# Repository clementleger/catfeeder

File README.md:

catfeeder
=========

Arduino scripts for cat feeder

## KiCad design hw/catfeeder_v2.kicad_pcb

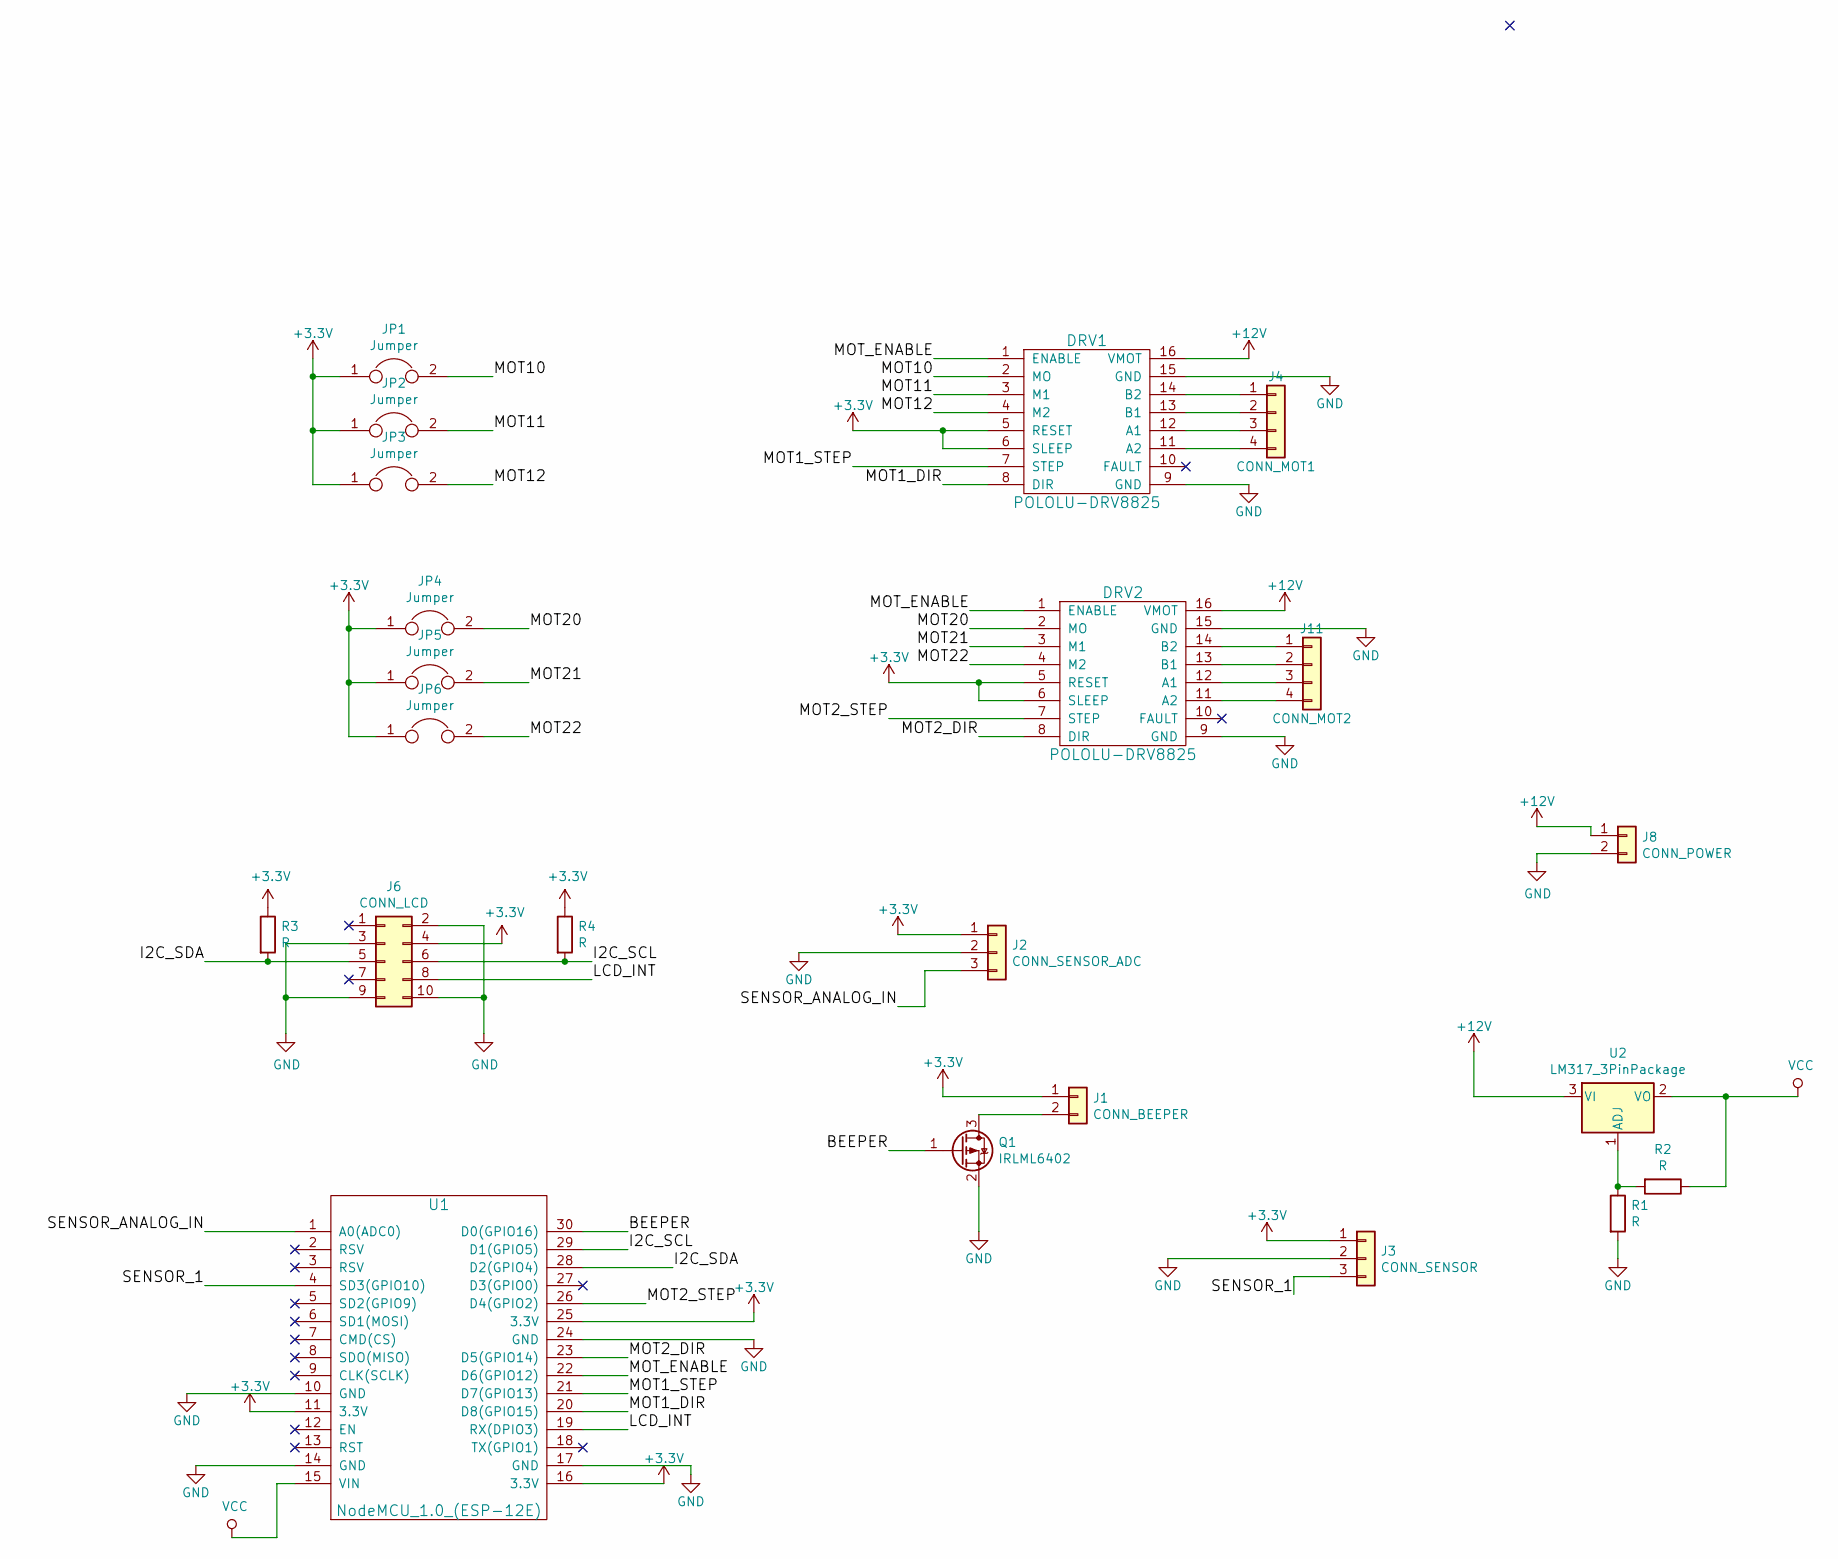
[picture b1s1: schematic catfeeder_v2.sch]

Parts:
DRV1, DRV2: POLOLU-DRV8825
J1: CONN_BEEPER; JST_XH_B02B-XH-A_1x02_P2.50mm_Vertical
J2: CONN_SENSOR_ADC; JST_XH_B03B-XH-A_1x03_P2.50mm_Vertical
J3: CONN_SENSOR; JST_XH_B03B-XH-A_1x03_P2.50mm_Vertical
J4: CONN_MOT1; JST_XH_B04B-XH-A_1x04_P2.50mm_Vertical
J6: CONN_LCD; IDC-Header_2x05_P2.54mm_Vertical
J8: CONN_POWER; TerminalBlock_bornier-2_P5.08mm
J11: CONN_MOT2; JST_XH_B04B-XH-A_1x04_P2.50mm_Vertical
JP1, JP2, JP3, JP4, JP5, JP6: Jumper; R_0805_2012Metric_Pad1.15x1.40mm_HandSolder
Q1: IRLML6402; SOT-23
R1, R2: R; R_0805_2012Metric_Pad1.15x1.40mm_HandSolder
R3, R4: R; R_Axial_DIN0207_L6.3mm_D2.5mm_P10.16mm_Horizontal
U1: NodeMCU_1.0_(ESP-12E); ESP12F-Devkit-V3
U2: LM317_3PinPackage; TO-220-3_Vertical

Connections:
+3V3: DRV1.5 (RESET), DRV1.6 (SLEEP), DRV2.5 (RESET), DRV2.6 (SLEEP), J1.1, J2.1, J3.1, J6.4, JP1.1, JP2.1, JP3.1, JP4.1, JP5.1, JP6.1, R3.1, R4.1, U1.11 (3.3V), U1.16 (3.3V), U1.25 (3.3V)
+12V: DRV1.16 (VMOT), DRV2.16 (VMOT), J8.1, U2.3 (VI)
/BEEPER: Q1.1 (G), U1.30 (D0(GPIO16))
/I2C_SCL: J6.6, R4.2, U1.29 (D1(GPIO5))
/I2C_SDA: J6.5, R3.2, U1.28 (D2(GPIO4))
/LCD_INT: J6.8, U1.19 (RX(DPIO3))
/MOT1_DIR: DRV1.8 (DIR), U1.20 (D8(GPIO15))
/MOT1_STEP: DRV1.7 (STEP), U1.21 (D7(GPIO13))
/MOT2_DIR: DRV2.8 (DIR), U1.23 (D5(GPIO14))
/MOT2_STEP: DRV2.7 (STEP), U1.26 (D4(GPIO2))
/MOT10: DRV1.2 (MO), JP1.2
/MOT11: DRV1.3 (M1), JP2.2
/MOT12: DRV1.4 (M2), JP3.2
/MOT20: DRV2.2 (MO), JP4.2
/MOT21: DRV2.3 (M1), JP5.2
/MOT22: DRV2.4 (M2), JP6.2
/MOT_ENABLE: DRV1.1 (ENABLE), DRV2.1 (ENABLE), U1.22 (D6(GPIO12))
/SENSOR_1: J3.3, U1.4 (SD3(GPIO10))
/SENSOR_ANALOG_IN: J2.3, U1.1 (A0(ADC0))
GND: DRV1.9 (GND), DRV1.15 (GND), DRV2.9 (GND), DRV2.15 (GND), J2.2, J3.2, J6.2, J6.3, J6.9, J6.10, J8.2, Q1.2 (S), R1.2, U1.10 (GND), U1.14 (GND), U1.17 (GND), U1.24 (GND)
unnamed: DRV1.11 (A2), J4.4
unnamed: DRV1.12 (A1), J4.3
unnamed: DRV1.13 (B1), J4.2
unnamed: DRV1.14 (B2), J4.1
unnamed: DRV2.11 (A2), J11.4
unnamed: DRV2.12 (A1), J11.3
unnamed: DRV2.13 (B1), J11.2
unnamed: DRV2.14 (B2), J11.1
unnamed: J1.2, Q1.3 (D)
unnamed: R1.1, R2.2, U2.1 (ADJ)
VCC: R2.1, U1.15 (VIN), U2.2 (VO)

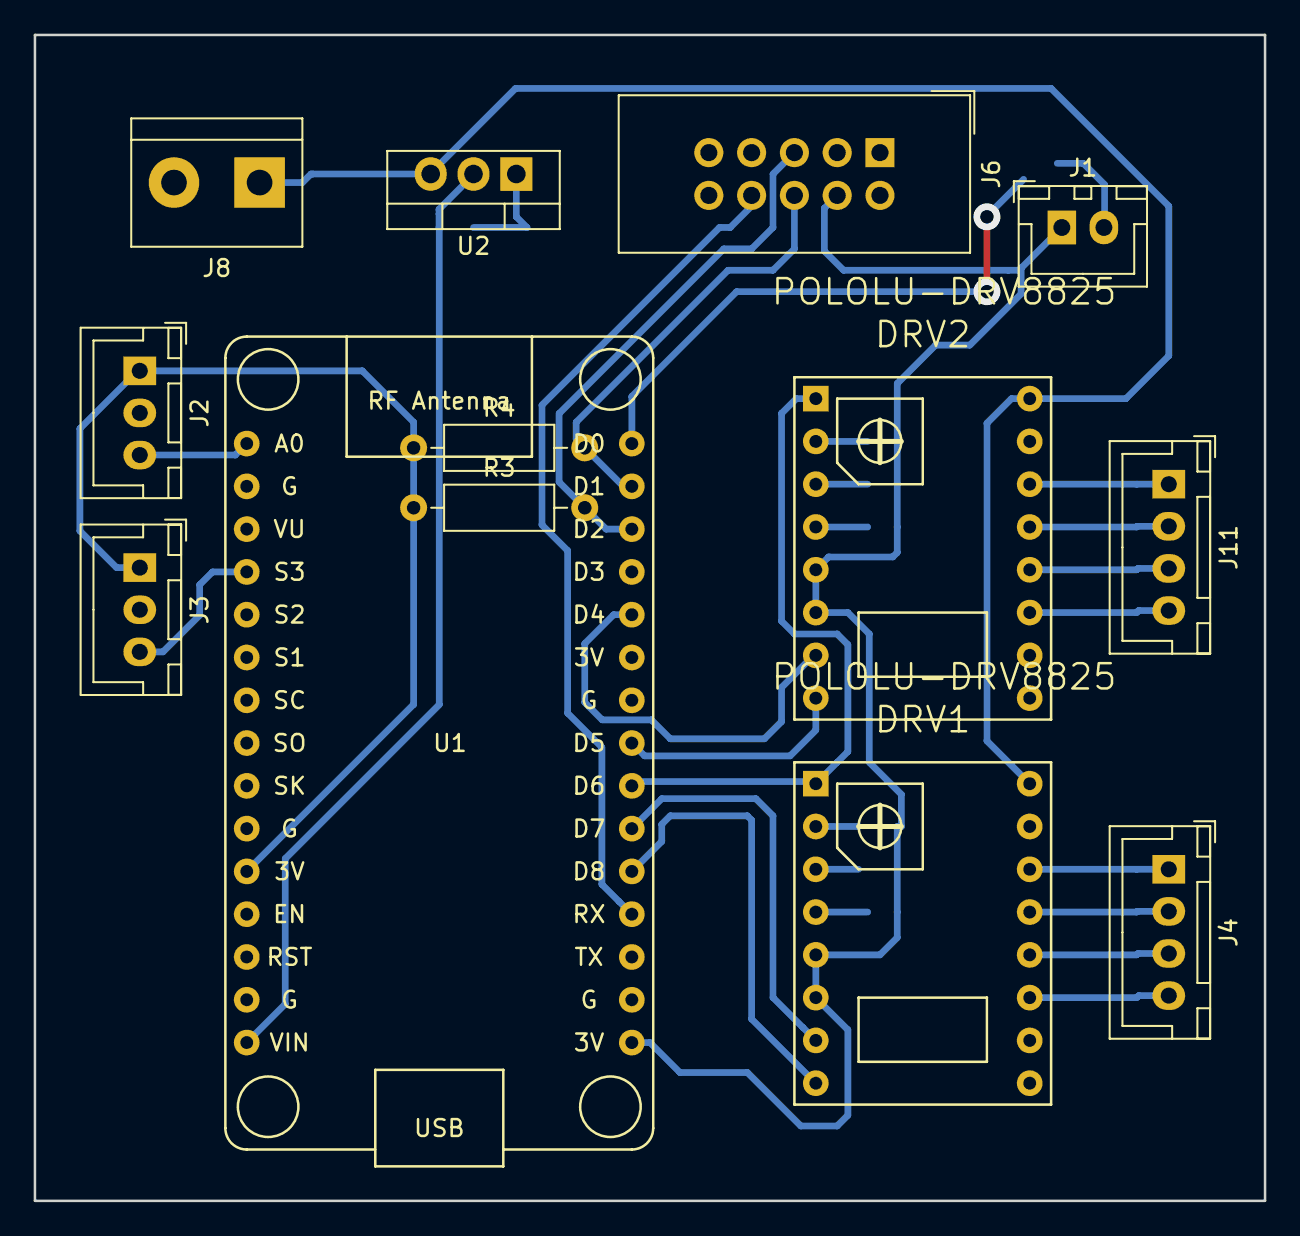
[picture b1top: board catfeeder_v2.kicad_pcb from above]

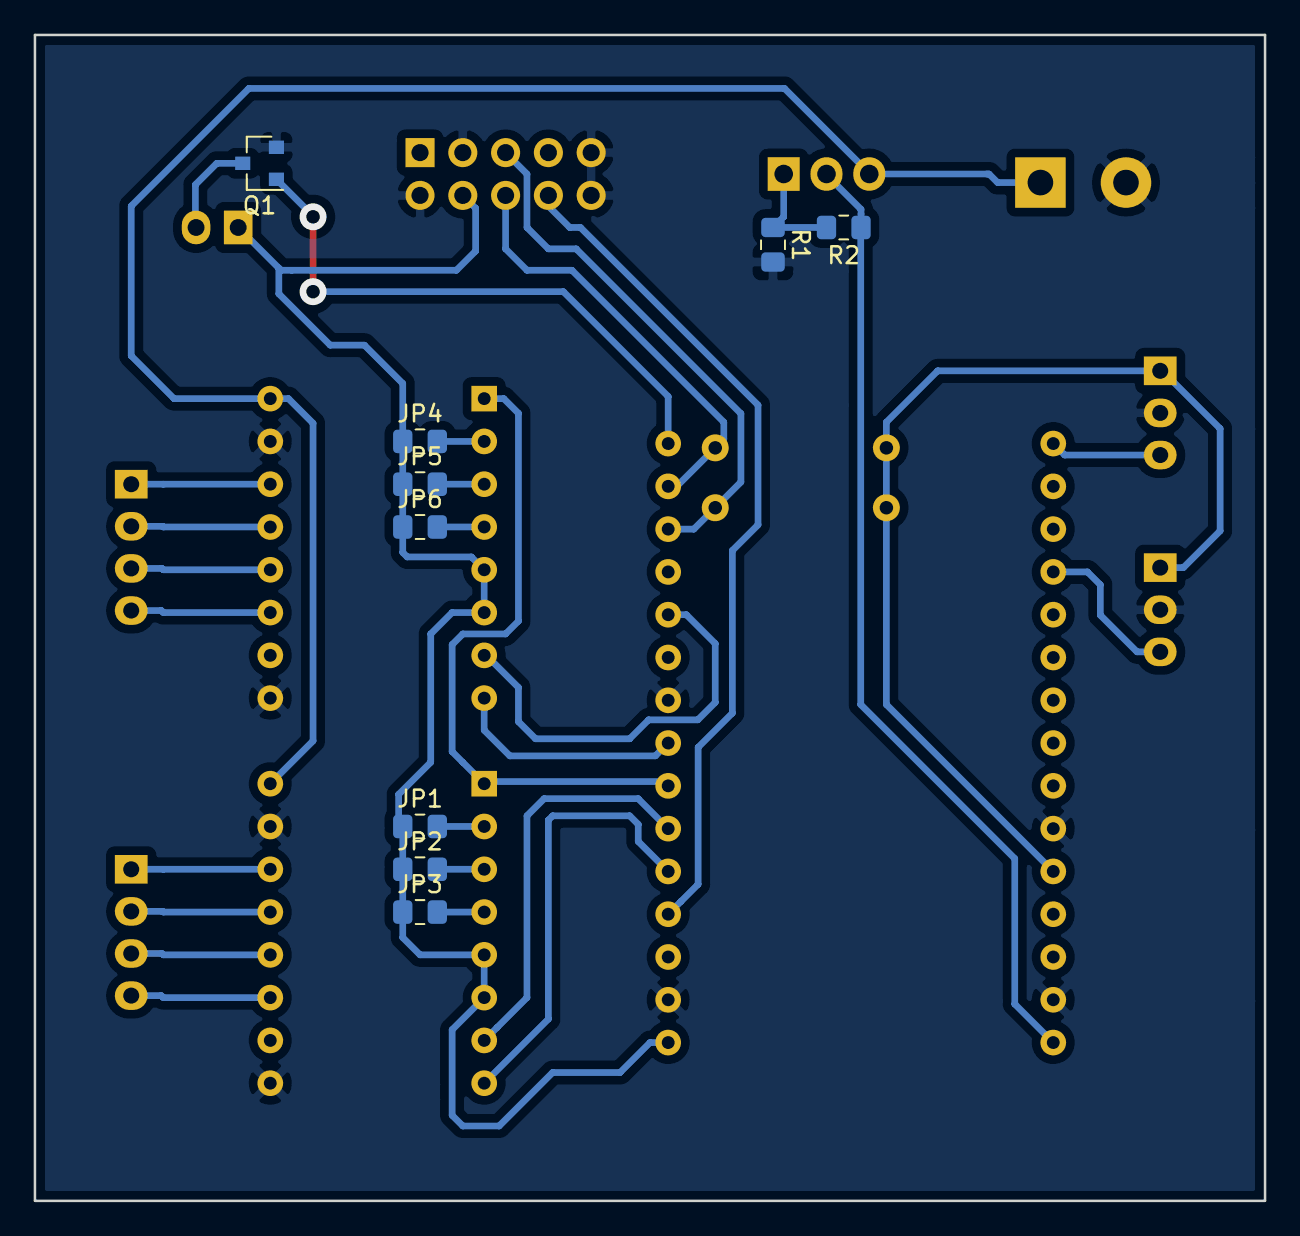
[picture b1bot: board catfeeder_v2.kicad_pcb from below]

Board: 2 copper layers, 73.0 x 69.2 mm, 22 parts (9 on the bottom side), 31 nets.

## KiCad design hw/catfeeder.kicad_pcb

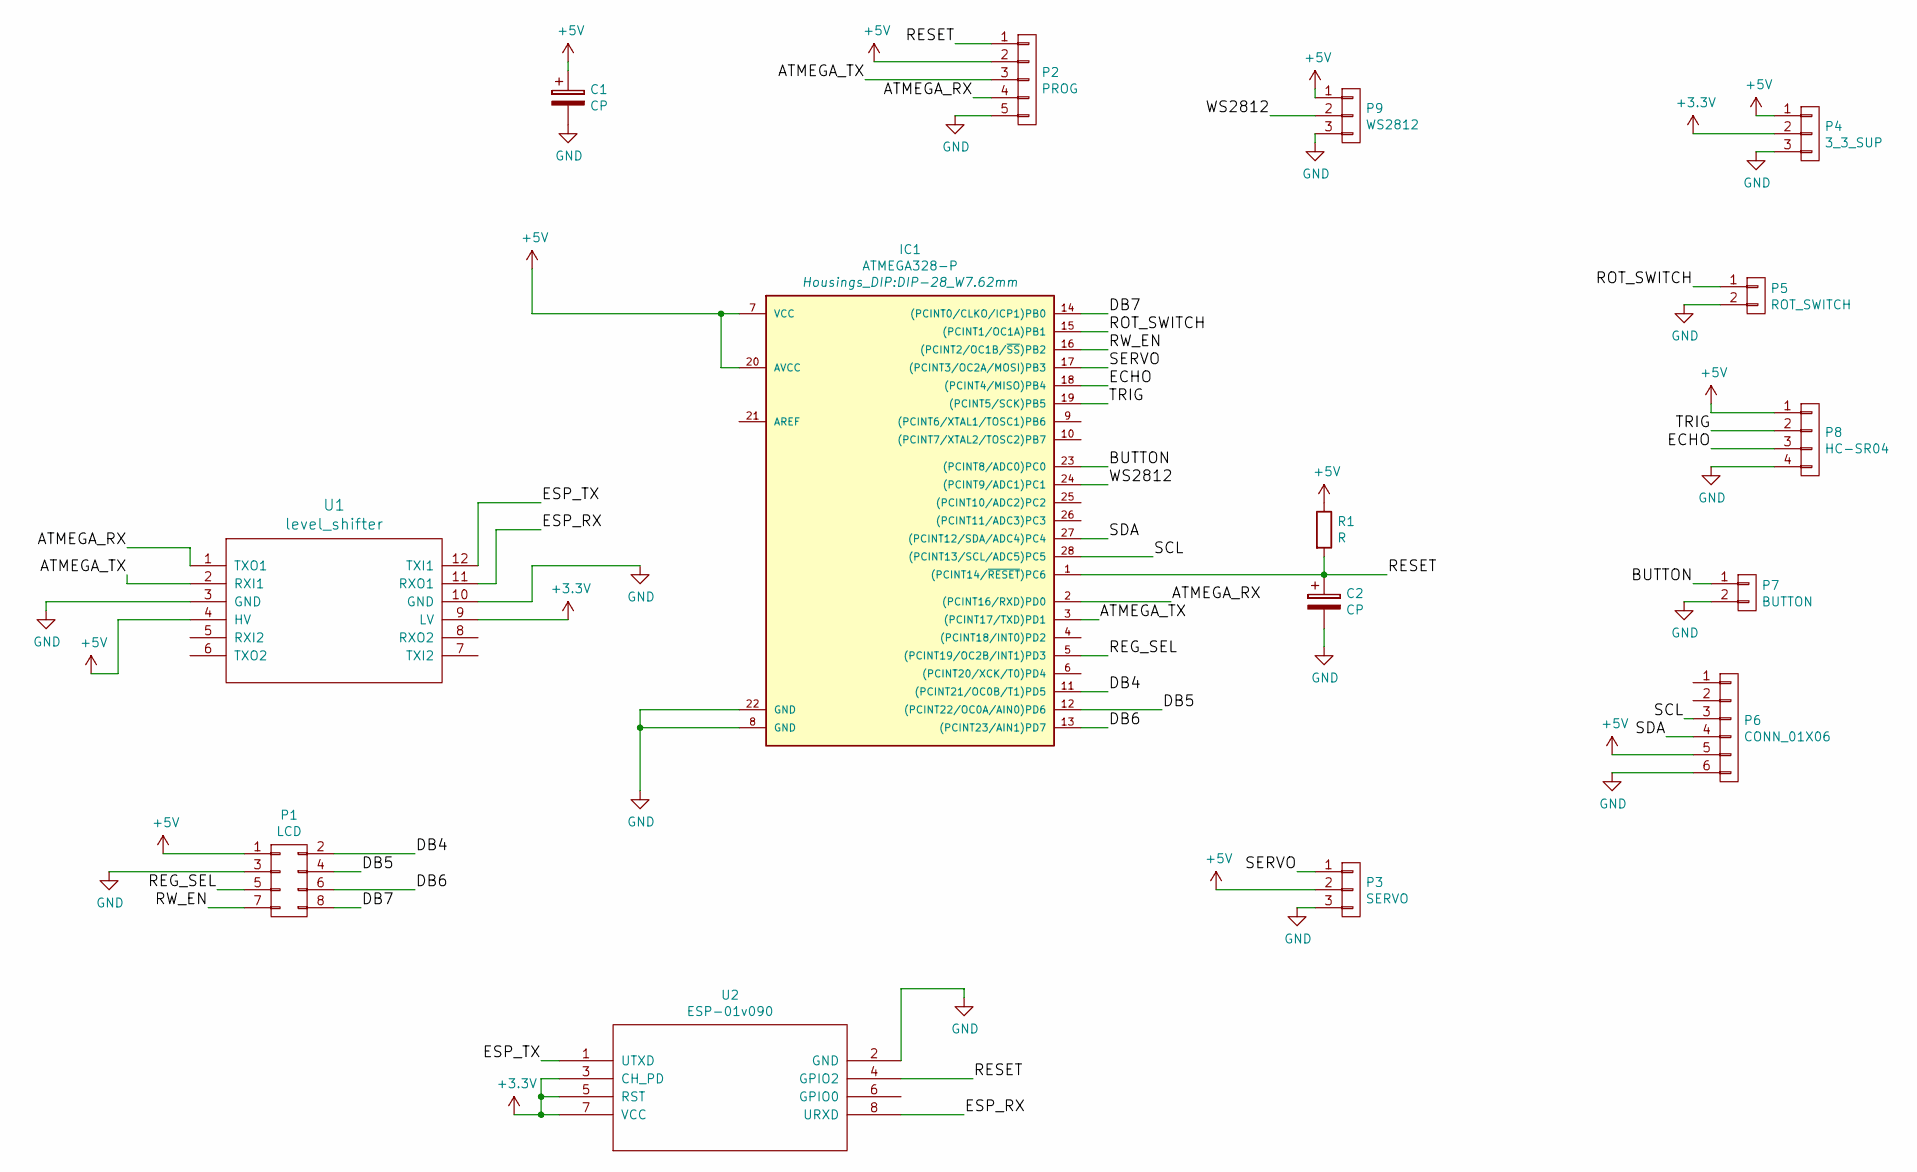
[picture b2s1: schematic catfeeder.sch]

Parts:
C1, C2: CP; C_Radial_D5_L11_P2
IC1: ATMEGA328-P; DIP-28_W7.62mm
P1: LCD; Pin_Header_Straight_2x04
P2: PROG; Pin_Header_Straight_1x05
P3: SERVO; Pin_Header_Straight_1x03
P4: 3_3_SUP; Pin_Header_Straight_1x03
P5: ROT_SWITCH; Pin_Header_Straight_1x02
P6: CONN_01X06; Pin_Header_Straight_1x06
P7: BUTTON; Pin_Header_Straight_1x02
P8: HC-SR04; Pin_Header_Straight_1x04
P9: WS2812; Pin_Header_Straight_1x03
R1: R; Resistor_Horizontal_RM7mm
U1: level_shifter
U2: ESP-01v090; Pin_Header_Straight_2x04

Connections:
+3V3: P4.2, U1.9 (LV), U2.3 (CH_PD), U2.5 (RST), U2.7 (VCC)
+5V: C1.1, IC1.7 (VCC), IC1.20 (AVCC), P1.1, P2.2, P3.2, P4.1, P6.5, P8.1, P9.1, R1.1, U1.4 (HV)
/ATMEGA_RX: IC1.2 ((PCINT16/RXD)PD0), P2.4, U1.1 (TXO1)
/ATMEGA_TX: IC1.3 ((PCINT17/TXD)PD1), P2.3, U1.2 (RXI1)
/BUTTON: IC1.23 ((PCINT8/ADC0)PC0), P7.1
/DB4: IC1.11 ((PCINT21/OC0B/T1)PD5), P1.2
/DB5: IC1.12 ((PCINT22/OC0A/AIN0)PD6), P1.4
/DB6: IC1.13 ((PCINT23/AIN1)PD7), P1.6
/DB7: IC1.14 ((PCINT0/CLKO/ICP1)PB0), P1.8
/ECHO: IC1.18 ((PCINT4/MISO)PB4), P8.3
/ESP_RX: U1.11 (RXO1), U2.8 (URXD)
/ESP_TX: U1.12 (TXI1), U2.1 (UTXD)
/REG_SEL: IC1.5 ((PCINT19/OC2B/INT1)PD3), P1.5
/RESET: C2.1, IC1.1 ((PCINT14/~RESET~)PC6), P2.1, R1.2, U2.4 (GPIO2)
/ROT_SWITCH: IC1.15 ((PCINT1/OC1A)PB1), P5.1
/RW_EN: IC1.16 ((PCINT2/OC1B/~SS~)PB2), P1.7
/SCL: IC1.28 ((PCINT13/SCL/ADC5)PC5), P6.3
/SDA: IC1.27 ((PCINT12/SDA/ADC4)PC4), P6.4
/SERVO: IC1.17 ((PCINT3/OC2A/MOSI)PB3), P3.1
/TRIG: IC1.19 ((PCINT5/SCK)PB5), P8.2
/WS2812: IC1.24 ((PCINT9/ADC1)PC1), P9.2
GND: C1.2, C2.2, IC1.8 (GND), IC1.22 (GND), P1.3, P2.5, P3.3, P4.3, P5.2, P6.6, P7.2, P8.4, P9.3, U1.3 (GND), U1.10 (GND), U2.2 (GND)

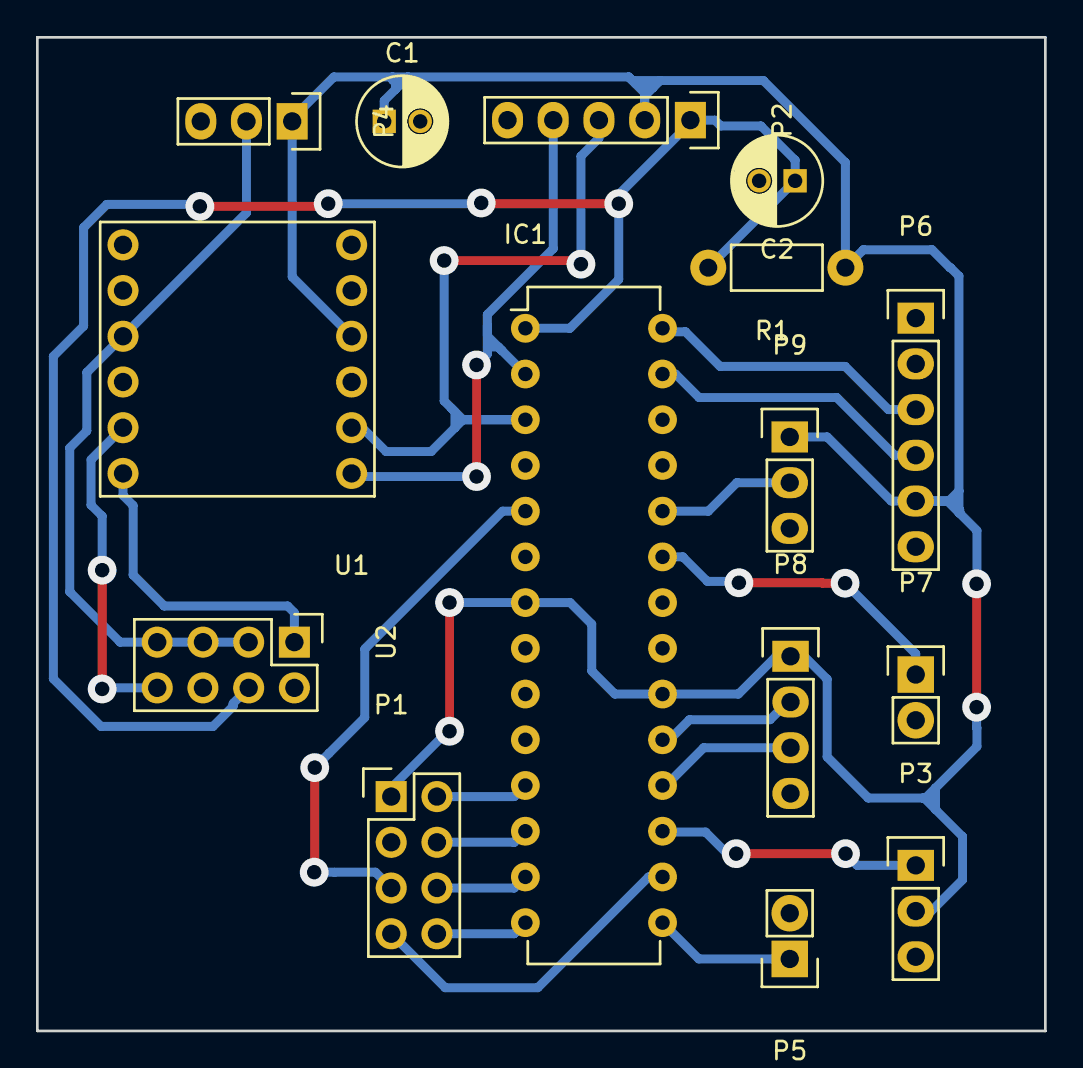
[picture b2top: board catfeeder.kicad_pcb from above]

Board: 2 copper layers, 56.0 x 55.2 mm, 15 parts (0 on the bottom side), 22 nets.

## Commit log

2015-01-22 Menu: handle menu more cleanly
2015-01-24 Src: add menu for feeding
2015-02-02 Ino: add time checking for feeding and statistics
2015-02-06 Lots of improvement, save to eeprom and statistics
2015-02-08 Script: reorder menu for faster access
2015-02-09 Menu: use recursive function for better menu handling
2015-02-10 Cleanup in defines Use float for gram per portions and other stuff
2015-02-11 Catfeeder: reorder pins
2015-02-12 Add raspberry Pi code
2015-02-12 Move folder back to top
2015-02-12 Arduino: move files for Arduino IDE
2015-02-15 RF: add support for remote feeding
2015-02-15 Add RF24 as submodule
2015-02-15 Add DS1302 as submodule
2015-02-16 Catfeeder: enhance protocol for cat feeding
2015-02-28 Arduino: 8 slot instead of 3, command to get statistics
2015-02-28 Raspberry PI: use libmicrohttpd to handle connections
2015-02-28 Arduino: do not send any response back to the host whan setting slot
2015-03-12 Raspi: fix MHD wrong type for buffer
2015-03-14 Protocol: add a settime command
2015-03-14 Arduino: Remove serial print
2015-03-14 Server: fix wrong value for setslot command
2015-03-14 Raspi: bind web server to loopback address only
2015-03-14 Web: Use only local ressources URL
2015-03-14 Files: remove useless script
2015-03-14 Remove useless files and better favicon
2015-03-14 Web: add title to webpage
2015-03-14 Web: liveupdate of total qty per day
2015-03-15 Web: simpler UI
2015-03-15 Web: add notification for actions
2015-03-23 Arduino: save slot after setting recevied from radio
2015-03-27 Rename force feed into manual feed
2015-03-29 Web: fix duplicated span id
2015-06-08 Add a communication enum to get time
2015-08-03 Arduino: add a timeout on feeder to detect blocked mecanism Raspberry: report the value on web interface
2016-06-19 Add schematic
2016-06-26 Modify schematic to avoid gnd via
2016-11-03 Add clock settings to sketch
2016-11-03 Update catfeeder schematics
2018-05-27 First V2 Schematic
2018-09-02 Use submodule for esp footprint
2018-09-03 Add mounting holes
2019-08-24 Add first arduino sketch
2019-08-25 hw: Add missing pullup resistors for I2C
2019-08-25 Fix esp12f spacing
2019-08-25 sw: First proto sketch
2019-08-25 Move INTPIN to GPIO3
2019-08-27 ST7306: Fix inverted parameters for setCursor
2019-08-27 Port old catfeeder code to new platform
2019-09-01 sw: bring back eeprom support
2019-09-01 sw: reenable time fetching and display
2019-09-08 Add beasic stepper and web support
2019-10-05 Add feeding to webserver
2019-11-19 Add stepper driver library
2019-11-19 sw: handle stepper motor properly
